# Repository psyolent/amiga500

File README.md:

# RE-Amiga500
Amiga 500+ v8a Re-Imagined.

These files are generated from schematics. Not from a printed circuit board via Sprint (like my A2000 I will soon release)
https://www.amigawiki.org/dnl/schematics/A500_R6.pdf 

I manually routed these traces. The component positioning needs to be checked for accuracy and the mounting holes (at time of release need to be added)

I am releasing these for people to use not for commercial purposes to keep the Amiga alive. It is part of who I am and will live on with me forever along this journey.

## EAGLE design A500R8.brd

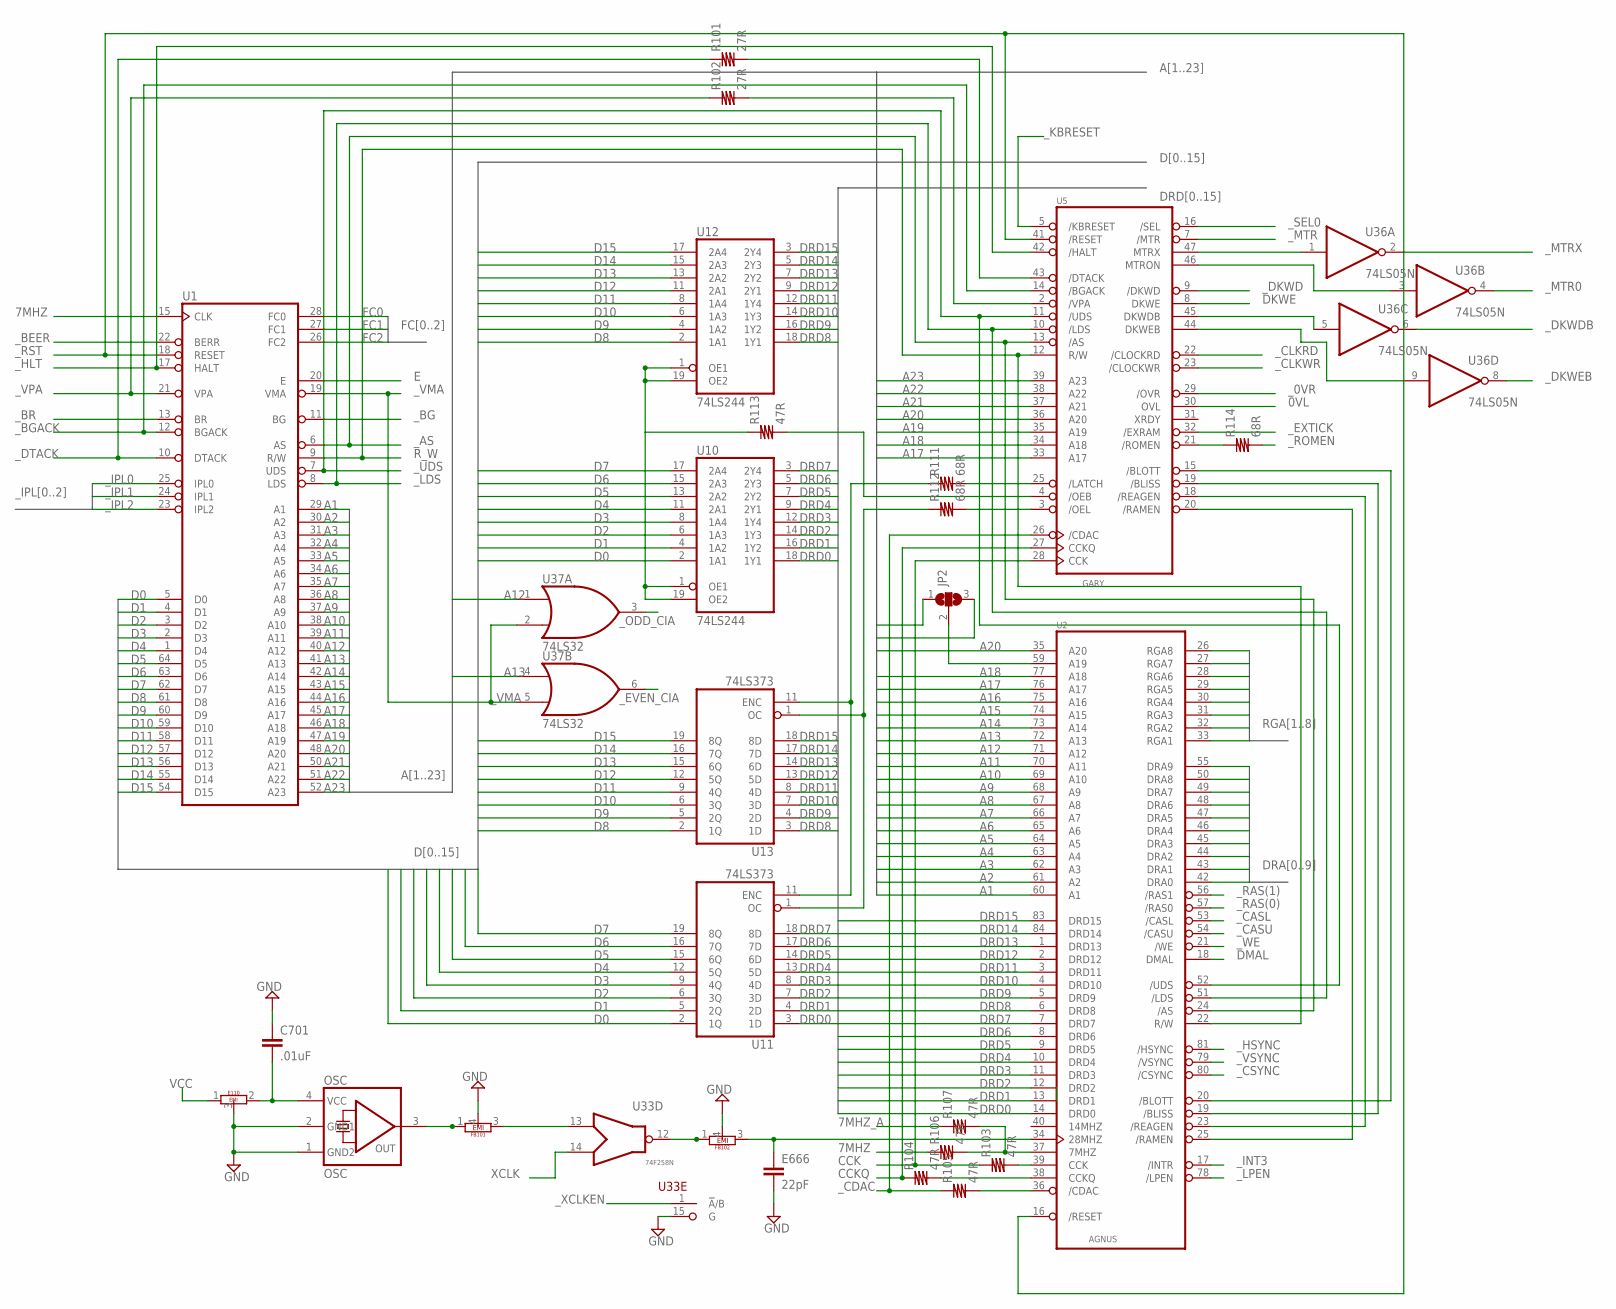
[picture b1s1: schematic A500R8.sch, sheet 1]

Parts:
C701: .01uF; C10B4
E110: EMIFILTER
E666: 22pF; C10B4
FB101: 68R; EMIFILTLONG
FB102: 150; EMIFILTLONG
JP2: SJ2W; SJ_2
OSC: OSC; AMIGACRYSTAL
R101, R102: 27R; R10B4
R103, R104, R105, R106, R107, R113: 47R; R10B4
R111, R112, R114: 68R; R10B4
U1: MC68000P; DIL64
U2: AGNU8375; PLCC84
U5: GARY; DIP48-6
U10, U12: 74LS244; DIL20
U11, U13: 74LS373; DIL20
U33: 74F258N; DIL16
U36: 74LS05N; DIL14
U37: 74LS32; DIL14

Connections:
0VL: U5.30 (OVL); also elsewhere on the board
7MHZ: R106.1, U1.15 (CLK); also elsewhere on the board
7MHZ_A: R107.1; also elsewhere on the board
A1: U1.29 (A1), U2.60 (A1); also elsewhere on the board
A2: U1.30 (A2), U2.61 (A2); also elsewhere on the board
A3: U1.31 (A3), U2.62 (A3); also elsewhere on the board
A4: U1.32 (A4), U2.63 (A4); also elsewhere on the board
A5: U1.33 (A5), U2.64 (A5); also elsewhere on the board
A6: U1.34 (A6), U2.65 (A6); also elsewhere on the board
A7: U1.35 (A7), U2.66 (A7); also elsewhere on the board
A8: U1.36 (A8), U2.67 (A8); also elsewhere on the board
A9: U1.37 (A9), U2.68 (A9); also elsewhere on the board
A10: U1.38 (A10), U2.69 (A10); also elsewhere on the board
A11: U1.39 (A11), U2.70 (A11); also elsewhere on the board
A12: U1.40 (A12), U2.71 (A12), U37.1 (I0); also elsewhere on the board
A13: U1.41 (A13), U2.72 (A13), U37.4 (I0); also elsewhere on the board
A14: U1.42 (A14), U2.73 (A14); also elsewhere on the board
A15: U1.43 (A15), U2.74 (A15); also elsewhere on the board
A16: U1.44 (A16), U2.75 (A16); also elsewhere on the board
A17: U1.45 (A17), U2.76 (A17), U5.33 (A17); also elsewhere on the board
A18: U1.46 (A18), U2.77 (A18), U5.34 (A18); also elsewhere on the board
A19: JP2.3, U1.47 (A19), U5.35 (A19); also elsewhere on the board
A20: U1.48 (A20), U2.35 (A20), U5.36 (A20); also elsewhere on the board
A21: U1.50 (A21), U5.37 (A21); also elsewhere on the board
A22: U1.51 (A22), U5.38 (A22); also elsewhere on the board
A23: JP2.1, U1.52 (A23), U5.39 (A23); also elsewhere on the board
CCK: R103.1, U5.28 (CCK); also elsewhere on the board
CCKQ: R104.1, U5.27 (CCKQ); also elsewhere on the board
D0: U1.5 (D0), U10.2 (1A1), U11.2 (1Q); also elsewhere on the board
D1: U1.4 (D1), U10.4 (1A2), U11.5 (2Q); also elsewhere on the board
D2: U1.3 (D2), U10.6 (1A3), U11.6 (3Q); also elsewhere on the board
D3: U1.2 (D3), U10.8 (1A4), U11.9 (4Q); also elsewhere on the board
D4: U1.1 (D4), U10.11 (2A1), U11.12 (5Q); also elsewhere on the board
D5: U1.64 (D5), U10.13 (2A2), U11.15 (6Q); also elsewhere on the board
D6: U1.63 (D6), U10.15 (2A3), U11.16 (7Q); also elsewhere on the board
D7: U1.62 (D7), U10.17 (2A4), U11.19 (8Q); also elsewhere on the board
D8: U1.61 (D8), U12.2 (1A1), U13.2 (1Q); also elsewhere on the board
D9: U1.60 (D9), U12.4 (1A2), U13.5 (2Q); also elsewhere on the board
D10: U1.59 (D10), U12.6 (1A3), U13.6 (3Q); also elsewhere on the board
D11: U1.58 (D11), U12.8 (1A4), U13.9 (4Q); also elsewhere on the board
D12: U1.57 (D12), U12.11 (2A1), U13.12 (5Q); also elsewhere on the board
D13: U1.56 (D13), U12.13 (2A2), U13.15 (6Q); also elsewhere on the board
D14: U1.55 (D14), U12.15 (2A3), U13.16 (7Q); also elsewhere on the board
D15: U1.54 (D15), U12.17 (2A4), U13.19 (8Q); also elsewhere on the board
DKWE: U5.8 (DKWE); also elsewhere on the board
DMAL: U2.18 (DMAL); also elsewhere on the board
DRA0: U2.42 (DRA0); also elsewhere on the board
DRA1: U2.43 (DRA1); also elsewhere on the board
DRA2: U2.44 (DRA2); also elsewhere on the board
DRA3: U2.45 (DRA3); also elsewhere on the board
DRA4: U2.46 (DRA4); also elsewhere on the board
DRA5: U2.47 (DRA5); also elsewhere on the board
DRA6: U2.48 (DRA6); also elsewhere on the board
DRA7: U2.49 (DRA7); also elsewhere on the board
DRA8: U2.50 (DRA8); also elsewhere on the board
DRA9: U2.55 (DRA9); also elsewhere on the board
DRD0: U2.14 (DRD0), U10.18 (1Y1), U11.3 (1D); also elsewhere on the board
DRD1: U2.13 (DRD1), U10.16 (1Y2), U11.4 (2D); also elsewhere on the board
DRD2: U2.12 (DRD2), U10.14 (1Y3), U11.7 (3D); also elsewhere on the board
DRD3: U2.11 (DRD3), U10.12 (1Y4), U11.8 (4D); also elsewhere on the board
DRD4: U2.10 (DRD4), U10.9 (2Y1), U11.13 (5D); also elsewhere on the board
DRD5: U2.9 (DRD5), U10.7 (2Y2), U11.14 (6D); also elsewhere on the board
DRD6: U2.8 (DRD6), U10.5 (2Y3), U11.17 (7D); also elsewhere on the board
DRD7: U2.7 (DRD7), U10.3 (2Y4), U11.18 (8D); also elsewhere on the board
DRD8: U2.6 (DRD8), U12.18 (1Y1), U13.3 (1D); also elsewhere on the board
DRD9: U2.5 (DRD9), U12.16 (1Y2), U13.4 (2D); also elsewhere on the board
DRD10: U2.4 (DRD10), U12.14 (1Y3), U13.7 (3D); also elsewhere on the board
DRD11: U2.3 (DRD11), U12.12 (1Y4), U13.8 (4D); also elsewhere on the board
DRD12: U2.2 (DRD12), U12.9 (2Y1), U13.13 (5D); also elsewhere on the board
DRD13: U2.1 (DRD13), U12.7 (2Y2), U13.14 (6D); also elsewhere on the board
DRD14: U2.84 (DRD14), U12.5 (2Y3), U13.17 (7D); also elsewhere on the board
DRD15: U2.83 (DRD15), U12.3 (2Y4), U13.18 (8D); also elsewhere on the board
E: U1.20 (E); also elsewhere on the board
FC0: U1.28 (FC0); also elsewhere on the board
FC1: U1.27 (FC1); also elsewhere on the board
FC2: U1.26 (FC2); also elsewhere on the board
GND: C701.1, E110.3, E666.2, FB101.4, FB102.4, OSC.1 (GND2), OSC.2 (GND1), U2.41 (GND), U2.58 (GND), U2.82 (GND), U5.1 (GND), U5.24 (GND), U5.40 (GND), U33.15 (G); also elsewhere on the board
unnamed: R113.1, U10.1 (OE1), U10.19 (OE2), U12.1 (OE1), U12.19 (OE2)
unnamed: R113.2, U5.4 (/OEB)
unnamed: R112.1, U11.1 (OC), U13.1 (OC)
unnamed: R112.2, U5.3 (/OEL)
unnamed: R111.1, U11.11 (ENC), U13.11 (ENC)
unnamed: R111.2, U5.25 (/LATCH)
unnamed: R102.2, U5.2 (/VPA)
unnamed: R114.1, U5.21 (/ROMEN)
unnamed: U5.47 (MTRX), U36.1 (I)
unnamed: R101.2, U5.43 (/DTACK)
unnamed: R106.2, R107.2, U2.37 (7MHZ)
unnamed: R103.2, U2.39 (CCK)
unnamed: R104.2, U2.38 (CCKQ)
unnamed: R105.2, U2.36 (/CDAC)
unnamed: U2.20 (/BLOTT), U5.15 (/BLOTT)
unnamed: U2.19 (/BLISS), U5.19 (/BLISS)
unnamed: U2.23 (/REAGEN), U5.18 (/REAGEN)
unnamed: U2.25 (/RAMEN), U5.20 (/RAMEN)
unnamed: E666.1, FB102.3, U2.34 (28MHZ)
unnamed: JP2.2, U2.59 (A19)
unnamed: U5.46 (MTRON), U36.3 (I)
unnamed: U5.45 (DKWDB), U36.5 (I)
unnamed: U5.44 (DKWEB), U36.9 (I)
unnamed: FB102.1, FB102.2, U33.12 (O)
unnamed: FB101.1, FB101.2, OSC.3 (OUT)
unnamed: FB101.3, U33.13 (I0)
unnamed: C701.2, E110.2, OSC.4 (VCC)
RGA1: U2.33 (RGA1); also elsewhere on the board
RGA2: U2.32 (RGA2); also elsewhere on the board
RGA3: U2.31 (RGA3); also elsewhere on the board
RGA4: U2.30 (RGA4); also elsewhere on the board
RGA5: U2.29 (RGA5); also elsewhere on the board
RGA6: U2.28 (RGA6); also elsewhere on the board
RGA7: U2.27 (RGA7); also elsewhere on the board
RGA8: U2.26 (RGA8); also elsewhere on the board
R_W: U1.9 (R/W), U2.22 (R/W), U5.12 (R/W); also elsewhere on the board
VCC: E110.1; also elsewhere on the board
XCLK: U33.14 (I1); also elsewhere on the board
_0VR: U5.29 (/OVR); also elsewhere on the board
_AS: U1.6 (AS), U2.24 (/AS), U5.13 (/AS); also elsewhere on the board
_BEER: U1.22 (BERR); also elsewhere on the board
_BG: U1.11 (BG); also elsewhere on the board
_BGACK: U1.12 (BGACK), U5.14 (/BGACK); also elsewhere on the board
_BR: U1.13 (BR); also elsewhere on the board
_CASL: U2.53 (/CASL); also elsewhere on the board
_CASU: U2.54 (/CASU); also elsewhere on the board
_CDAC: R105.1, U5.26 (/CDAC); also elsewhere on the board
_CLKRD: U5.22 (/CLOCKRD); also elsewhere on the board
_CLKWR: U5.23 (/CLOCKWR); also elsewhere on the board
_CSYNC: U2.80 (/CSYNC); also elsewhere on the board
_DKWD: U5.9 (/DKWD); also elsewhere on the board
_DKWDB: U36.6 (O); also elsewhere on the board
_DKWEB: U36.8 (O); also elsewhere on the board
_DTACK: R101.1, U1.10 (DTACK); also elsewhere on the board
_EVEN_CIA: U37.6 (O); also elsewhere on the board
_EXTICK: U5.32 (/EXRAM); also elsewhere on the board
_HLT: U1.17 (HALT), U5.42 (/HALT); also elsewhere on the board
_HSYNC: U2.81 (/HSYNC); also elsewhere on the board
_INT3: U2.17 (/INTR); also elsewhere on the board
_IPL0: U1.25 (IPL0); also elsewhere on the board
_IPL1: U1.24 (IPL1); also elsewhere on the board
_IPL2: U1.23 (IPL2); also elsewhere on the board
_KBRESET: U5.5 (/KBRESET); also elsewhere on the board
_LDS: U1.8 (LDS), U2.51 (/LDS), U5.10 (/LDS); also elsewhere on the board
_LPEN: U2.78 (/LPEN); also elsewhere on the board
_MTR: U5.7 (/MTR); also elsewhere on the board
_MTR0: U36.4 (O); also elsewhere on the board
_MTRX: U36.2 (O); also elsewhere on the board
_ODD_CIA: U37.3 (O); also elsewhere on the board
_RAS(0): U2.57 (/RAS0); also elsewhere on the board
_RAS(1): U2.56 (/RAS1); also elsewhere on the board
_ROMEN: R114.2; also elsewhere on the board
_RST: U1.18 (RESET), U2.16 (/RESET), U5.41 (/RESET); also elsewhere on the board
_SEL0: U5.16 (/SEL); also elsewhere on the board
_UDS: U1.7 (UDS), U2.52 (/UDS), U5.11 (/UDS); also elsewhere on the board
_VMA: U1.19 (VMA), U37.2 (I1), U37.5 (I1); also elsewhere on the board
_VPA: R102.1, U1.21 (VPA); also elsewhere on the board
_VSYNC: U2.79 (/VSYNC); also elsewhere on the board
_WE: U2.21 (/WE); also elsewhere on the board
_XCLKEN: U33.1 (!A!/B); also elsewhere on the board

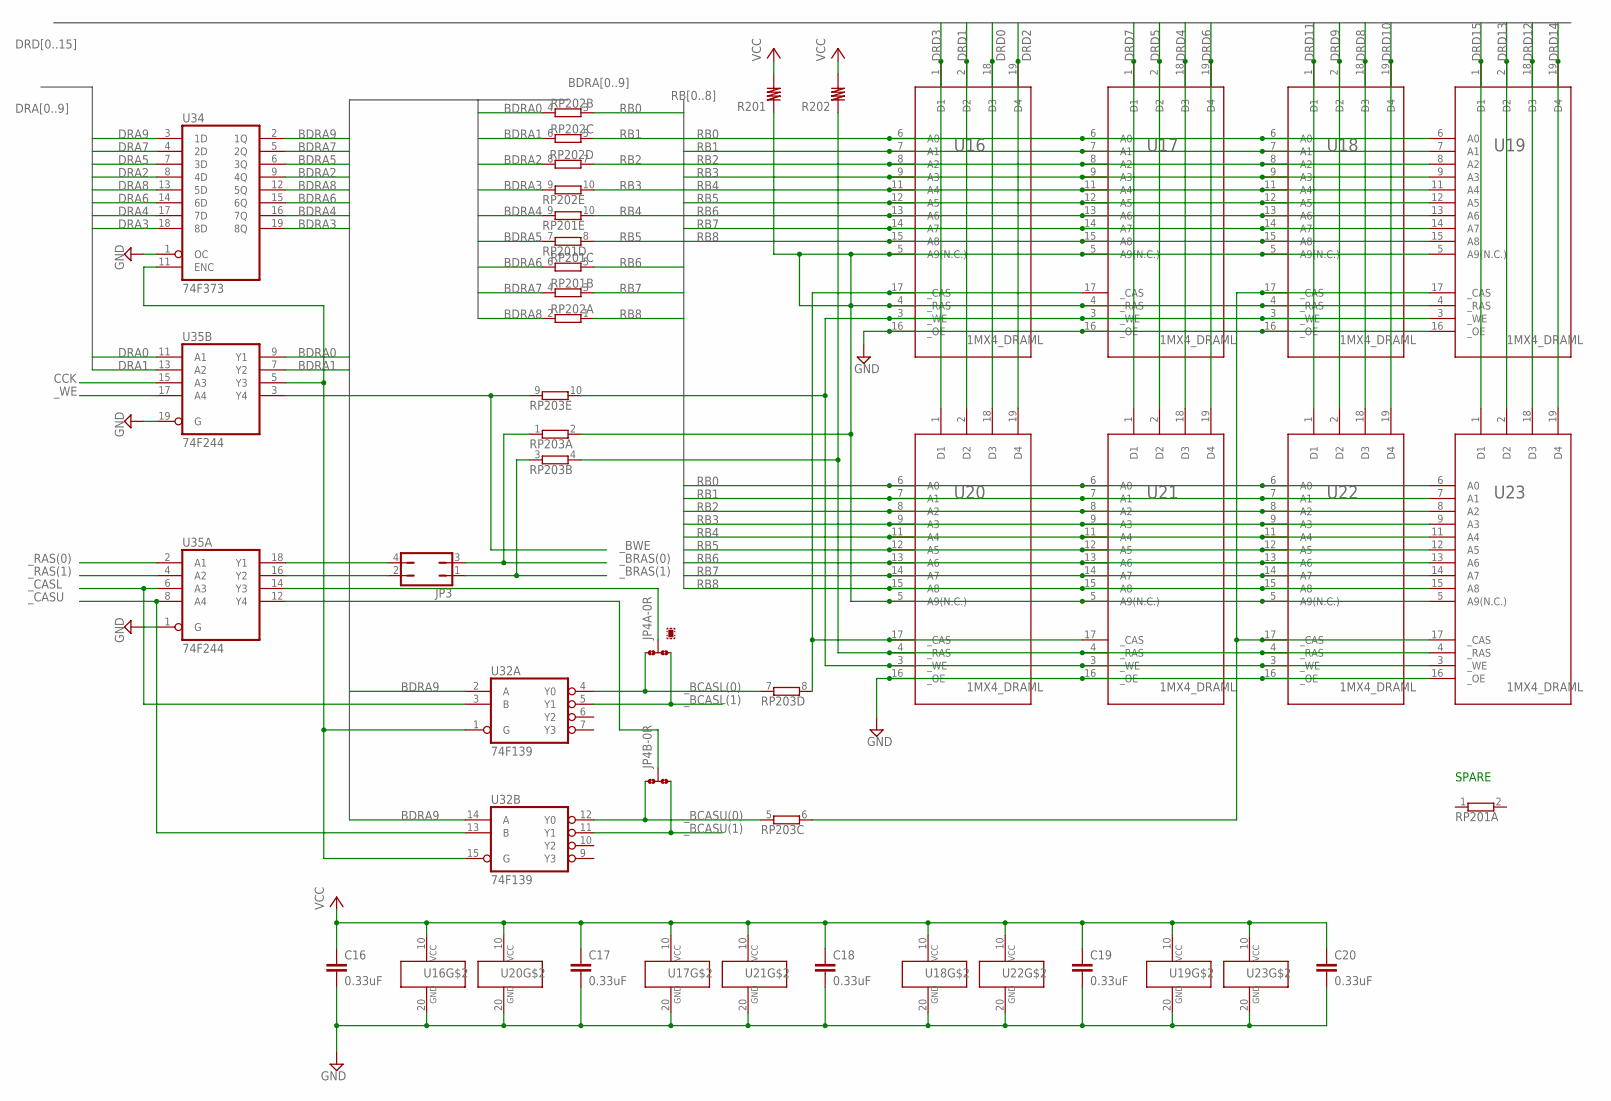
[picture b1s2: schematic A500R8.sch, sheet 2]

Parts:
C16, C17, C18, C19, C20: 0.33uF; C10B4
JP3: JP2Q
JP4A: JP4A; A0R-JMP
JP4B: JP4B; A0R-JMP
R201, R202: R10/4; R10B4
RP201, RP202, RP203: E5R; SIL10
U16, U17, U18, U19, U20, U21, U22, U23: 1MX4_DRAML; DIL20
U32: 74F139; DIL16
U34: 74F373; DIL20
U35: 74F244; DIL20

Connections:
BDRA0: RP202.4 (2), U35.9 (Y1); also elsewhere on the board
BDRA1: RP202.6 (2), U35.7 (Y2); also elsewhere on the board
BDRA2: RP202.8 (2), U34.9 (4Q); also elsewhere on the board
BDRA3: RP202.9 (1), U34.19 (8Q); also elsewhere on the board
BDRA4: RP201.9 (1), U34.16 (7Q); also elsewhere on the board
BDRA5: RP201.7 (1), U34.6 (3Q); also elsewhere on the board
BDRA6: RP201.6 (2), U34.15 (6Q); also elsewhere on the board
BDRA7: RP201.4 (2), U34.5 (2Q); also elsewhere on the board
BDRA8: RP202.2, U34.12 (5Q); also elsewhere on the board
BDRA9: U32.2 (A), U32.14 (A), U34.2 (1Q)
CCK: U35.15 (A3); also elsewhere on the board
DRA0: U35.11 (A1); also elsewhere on the board
DRA1: U35.13 (A2); also elsewhere on the board
DRA2: U34.8 (4D); also elsewhere on the board
DRA3: U34.18 (8D); also elsewhere on the board
DRA4: U34.17 (7D); also elsewhere on the board
DRA5: U34.7 (3D); also elsewhere on the board
DRA6: U34.14 (6D); also elsewhere on the board
DRA7: U34.4 (2D); also elsewhere on the board
DRA8: U34.13 (5D); also elsewhere on the board
DRA9: U34.3 (1D); also elsewhere on the board
DRD0: U16.18 (D3), U20.18 (D3); also elsewhere on the board
DRD1: U16.2 (D2), U20.2 (D2); also elsewhere on the board
DRD2: U16.19 (D4), U20.19 (D4); also elsewhere on the board
DRD3: U16.1 (D1), U20.1 (D1); also elsewhere on the board
DRD4: U17.18 (D3), U21.18 (D3); also elsewhere on the board
DRD5: U17.2 (D2), U21.2 (D2); also elsewhere on the board
DRD6: U17.19 (D4), U21.19 (D4); also elsewhere on the board
DRD7: U17.1 (D1), U21.1 (D1); also elsewhere on the board
DRD8: U18.18 (D3), U22.18 (D3); also elsewhere on the board
DRD9: U18.2 (D2), U22.2 (D2); also elsewhere on the board
DRD10: U18.19 (D4), U22.19 (D4); also elsewhere on the board
DRD11: U18.1 (D1), U22.1 (D1); also elsewhere on the board
DRD12: U19.18 (D3), U23.18 (D3); also elsewhere on the board
DRD13: U19.2 (D2), U23.2 (D2); also elsewhere on the board
DRD14: U19.19 (D4), U23.19 (D4); also elsewhere on the board
DRD15: U19.1 (D1), U23.1 (D1); also elsewhere on the board
GND: C16.2, C17.2, C18.2, C19.2, C20.2, U16.16 (_OE), U16.20 (GND1), U17.16 (_OE), U17.20 (GND1), U18.16 (_OE), U18.20 (GND1), U19.16 (_OE), U19.20 (GND1), U20.16 (_OE), U20.20 (GND1), U21.16 (_OE), U21.20 (GND1), U22.16 (_OE), U22.20 (GND1), U23.16 (_OE), U23.20 (GND1), U34.1 (OC), U35.1 (G), U35.19 (G); also elsewhere on the board
unnamed: U32.1 (G), U32.15 (G), U34.11 (ENC), U35.5 (Y3)
unnamed: JP3.4, U35.18 (Y1)
unnamed: JP3.2, U35.16 (Y2)
unnamed: JP4A.2, U35.14 (Y3)
unnamed: JP4B.2, U35.12 (Y4)
unnamed: R202.1, RP203.4 (2), U20.4 (_RAS), U21.4 (_RAS), U22.4 (_RAS), U23.4 (_RAS)
unnamed: RP203.6 (2), U18.17 (_CAS), U19.17 (_CAS), U22.17 (_CAS), U23.17 (_CAS)
unnamed: RP203.8 (2), U16.17 (_CAS), U17.17 (_CAS), U20.17 (_CAS), U21.17 (_CAS)
unnamed: RP203.10 (2), U16.3 (_WE), U17.3 (_WE), U18.3 (_WE), U19.3 (_WE), U20.3 (_WE), U21.3 (_WE), U22.3 (_WE), U23.3 (_WE)
unnamed: R201.1, RP203.2, U16.4 (_RAS), U16.5 (A9(N.C.)), U17.4 (_RAS), U17.5 (A9(N.C.)), U18.4 (_RAS), U18.5 (A9(N.C.)), U19.4 (_RAS), U19.5 (A9(N.C.)), U20.5 (A9(N.C.)), U21.5 (A9(N.C.)), U22.5 (A9(N.C.)), U23.5 (A9(N.C.))
RB0: RP202.3 (1), U16.6 (A0), U17.6 (A0), U18.6 (A0), U19.6 (A0), U20.6 (A0), U21.6 (A0), U22.6 (A0), U23.6 (A0)
RB1: RP202.5 (1), U16.7 (A1), U17.7 (A1), U18.7 (A1), U19.7 (A1), U20.7 (A1), U21.7 (A1), U22.7 (A1), U23.7 (A1)
RB2: RP202.7 (1), U16.8 (A2), U17.8 (A2), U18.8 (A2), U19.8 (A2), U20.8 (A2), U21.8 (A2), U22.8 (A2), U23.8 (A2)
RB3: RP202.10 (2), U16.9 (A3), U17.9 (A3), U18.9 (A3), U19.9 (A3), U20.9 (A3), U21.9 (A3), U22.9 (A3), U23.9 (A3)
RB4: RP201.10 (2), U16.11 (A4), U17.11 (A4), U18.11 (A4), U19.11 (A4), U20.11 (A4), U21.11 (A4), U22.11 (A4), U23.11 (A4)
RB5: RP201.8 (2), U16.12 (A5), U17.12 (A5), U18.12 (A5), U19.12 (A5), U20.12 (A5), U21.12 (A5), U22.12 (A5), U23.12 (A5)
RB6: RP201.5 (1), U16.13 (A6), U17.13 (A6), U18.13 (A6), U19.13 (A6), U20.13 (A6), U21.13 (A6), U22.13 (A6), U23.13 (A6)
RB7: RP201.3 (1), U16.14 (A7), U17.14 (A7), U18.14 (A7), U19.14 (A7), U20.14 (A7), U21.14 (A7), U22.14 (A7), U23.14 (A7)
RB8: RP202.1, U16.15 (A8), U17.15 (A8), U18.15 (A8), U19.15 (A8), U20.15 (A8), U21.15 (A8), U22.15 (A8), U23.15 (A8)
VCC: C16.1, C17.1, C18.1, C19.1, C20.1, R201.2, R202.2, U16.10 (VCC1), U17.10 (VCC1), U18.10 (VCC1), U19.10 (VCC1), U20.10 (VCC1), U21.10 (VCC1), U22.10 (VCC1), U23.10 (VCC1); also elsewhere on the board
_BCASL(0): JP4A.1, RP203.7 (1), U32.4 (Y0)
_BCASL(1): JP4A.3, U32.5 (Y1); also elsewhere on the board
_BCASU(0): JP4B.1, RP203.5 (1), U32.12 (Y0)
_BCASU(1): JP4B.3, U32.11 (Y1); also elsewhere on the board
_BRAS(0): JP3.3, RP203.1; also elsewhere on the board
_BRAS(1): JP3.1, RP203.3 (1); also elsewhere on the board
_BWE: RP203.9 (1), U35.3 (Y4); also elsewhere on the board
_CASL: U32.3 (B), U35.6 (A3); also elsewhere on the board
_CASU: U32.13 (B), U35.8 (A4); also elsewhere on the board
_RAS(0): U35.2 (A1); also elsewhere on the board
_RAS(1): U35.4 (A2); also elsewhere on the board
_WE: U35.17 (A4); also elsewhere on the board

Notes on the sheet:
SPARE

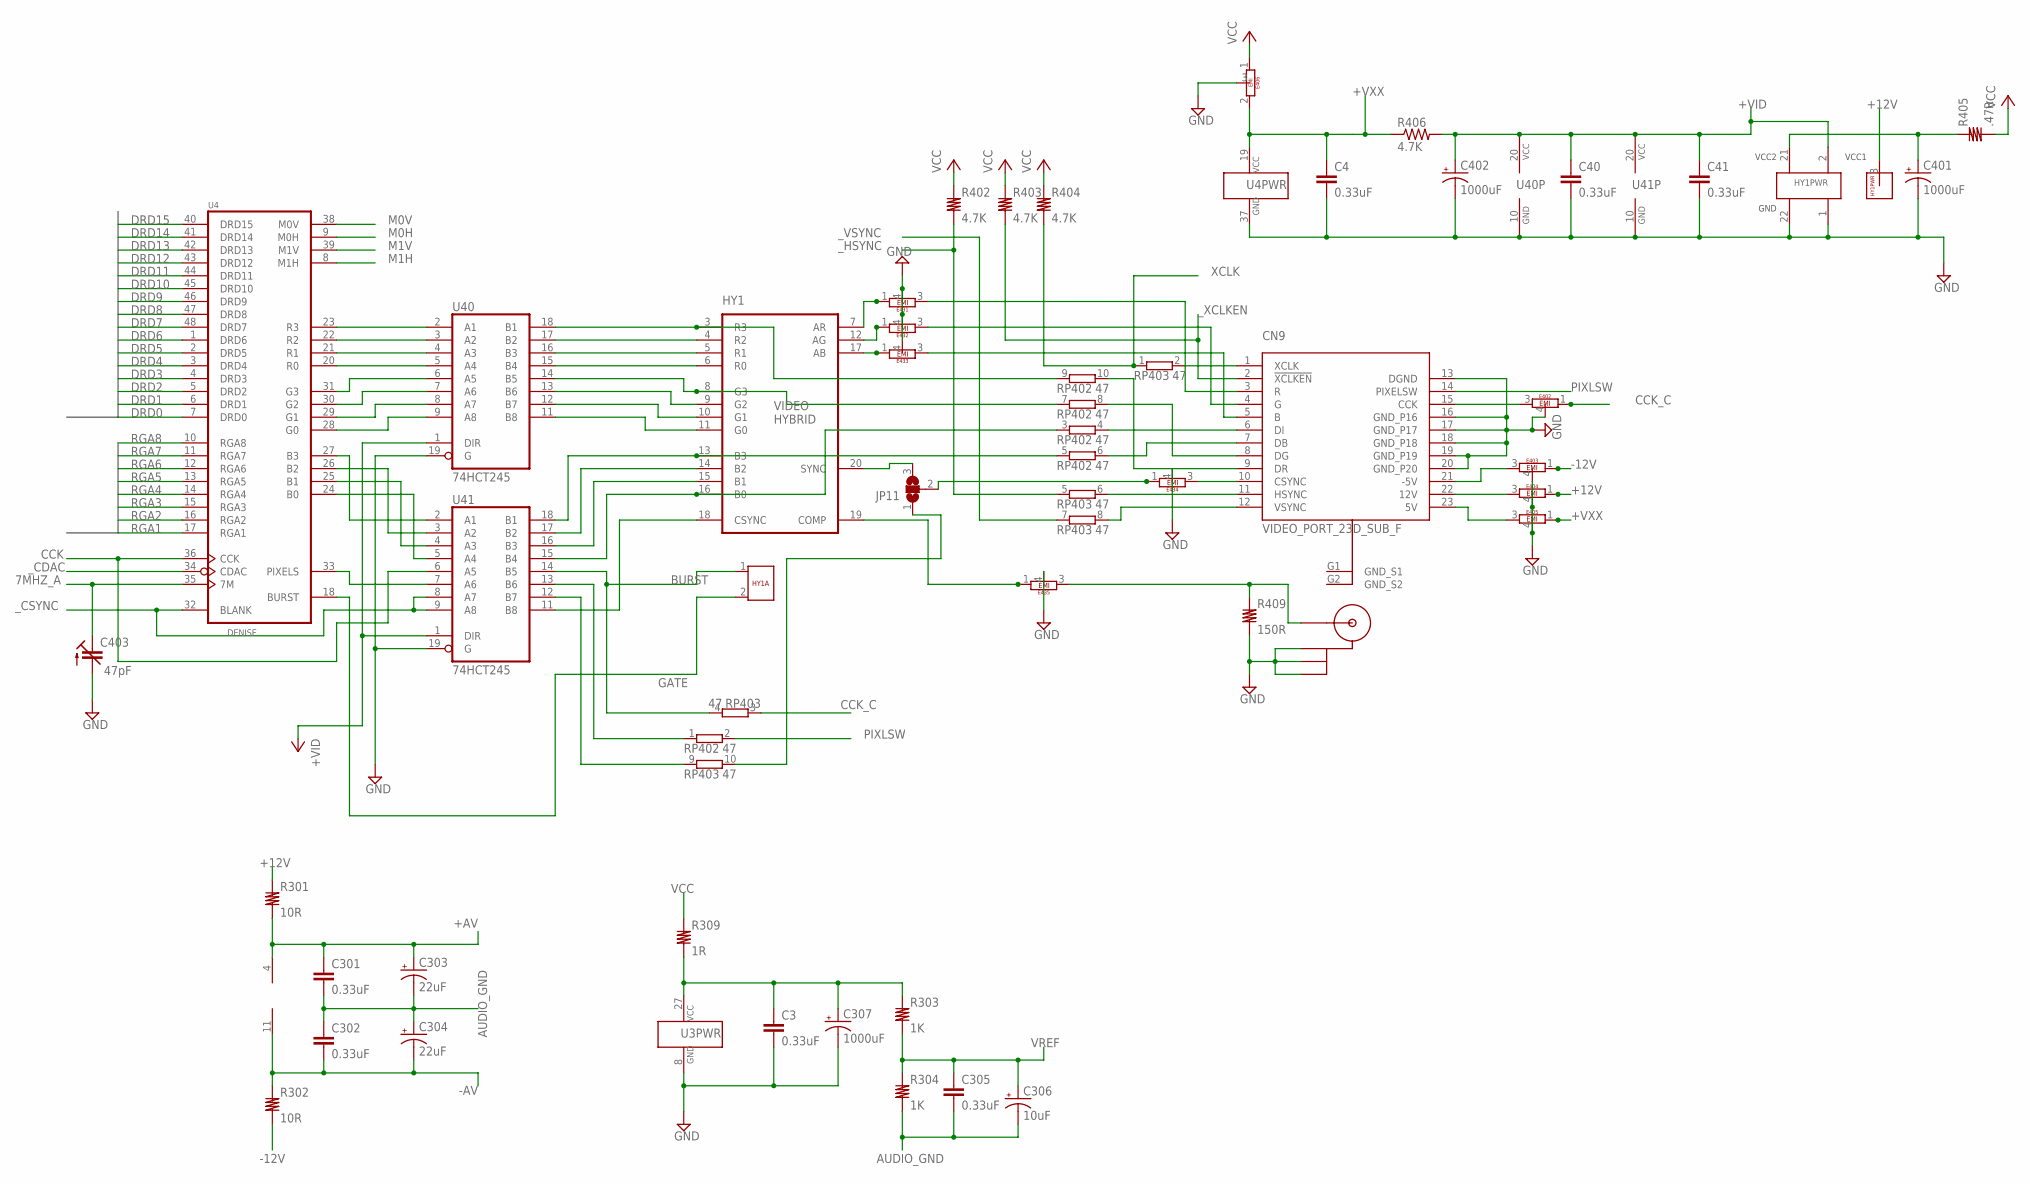
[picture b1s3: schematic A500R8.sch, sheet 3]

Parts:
C3, C4, C40, C41, C301, C302, C305: 0.33uF; C10B4
C303, C304: 22uF; E5-6
C306: 10uF; E5-6
C307: 1000uF; E5-6
C401, C402: 1000uF; E5-10,5
C403: 47pF; CTRIM3050.504
CN9: VIDEO_PORT_23D_SUB_F; F23H_FC
CN10: CINCH; CINCH-B
E402: 150pF; EMIFILTLONG
E403, E404, E405, E431, E432, E433, E434, E435: EMIFILTERLONG; EMIFILTLONG
E406: EMIFILTER
HY1: HY1; SIP22
JP11: SJ2W; SJ_2
R301, R302: 10R; R10B4
R303, R304: 1K; R10B4
R309: 1R; R10B4
R402, R403, R404: 4.7K; R10B4
R405: .47R; R10B4
R406: 4.7K; 0207/10
R409: 150R; R10B4
RP402, RP403: 47; SIL10
U3: PAULA_DIP; DIP48-6
U4: DENISE HR; DIP48-6
U14: LF347/TL084; DIL14
U40, U41: 74HCT245; DIL20
U$1: HY1A

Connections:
7MHZ_A: C403.1 (E), U4.35 (7M); also elsewhere on the board
+12V: E404.1, E404.2, R301.1, U$1.3; also elsewhere on the board
+AV: C301.1, C303.+, R301.2, U14.4 (V+); also elsewhere on the board
+VID: C40.1, C41.1, C402.+, HY1.2 (VCC), R406.2, U40.1 (DIR), U40.20 (VCC), U41.1 (DIR), U41.20 (VCC)
+VXX: C4.1, E405.1, E405.2, E406.2, R406.1, U4.19 (VCC1)
-12V: E403.1, E403.2, R302.2; also elsewhere on the board
-AV: C302.2, C304.-, R302.1, U14.11 (V-); also elsewhere on the board
AUDIO_GND: C301.2, C302.1, C303.-, C304.+, C305.2, C306.-, R304.2; also elsewhere on the board
BURST: RP403.4 (2), U41.14 (B5), U$1.1
CCK: U4.36 (CCK), U41.6 (A5); also elsewhere on the board
CCK_C: E402.1, E402.2, RP403.3 (1)
DRD0: U4.7 (DRD0); also elsewhere on the board
DRD1: U4.6 (DRD1); also elsewhere on the board
DRD2: U4.5 (DRD2); also elsewhere on the board
DRD3: U4.4 (DRD3); also elsewhere on the board
DRD4: U4.3 (DRD4); also elsewhere on the board
DRD5: U4.2 (DRD5); also elsewhere on the board
DRD6: U4.1 (DRD6); also elsewhere on the board
DRD7: U4.48 (DRD7); also elsewhere on the board
DRD8: U4.47 (DRD8); also elsewhere on the board
DRD9: U4.46 (DRD9); also elsewhere on the board
DRD10: U4.45 (DRD10); also elsewhere on the board
DRD11: U4.44 (DRD11); also elsewhere on the board
DRD12: U4.43 (DRD12); also elsewhere on the board
DRD13: U4.42 (DRD13); also elsewhere on the board
DRD14: U4.41 (DRD14); also elsewhere on the board
DRD15: U4.40 (DRD15); also elsewhere on the board
GATE: U4.18 (BURST), U$1.2
GND: C3.2, C4.2, C40.2, C41.2, C307.-, C401.-, C402.-, C403.2 (A), CN9.13 (DGND), CN9.16 (GND_P16), CN9.17 (GND_P17), CN9.18 (GND_P18), CN9.19 (GND_P19), CN9.20 (GND_P20), CN10.P$2, CN10.P$3, CN10.P$4, E402.4, E403.4, E404.4, E405.4, E406.3, E431.4, E432.4, E433.4, E434.4, E435.4, HY1.1 (GND), HY1.22 (GND), R409.2, U3.8 (GND1), U4.37 (GND1), U40.10 (GND), U40.19 (G), U41.10 (GND), U41.19 (G); also elsewhere on the board
GND_S1: CN9.G1 (GND_S1); also elsewhere on the board
GND_S2: CN9.G2 (GND_S2); also elsewhere on the board
M0H: U4.9 (M0H); also elsewhere on the board
M0V: U4.38 (M0V); also elsewhere on the board
M1H: U4.8 (M1H); also elsewhere on the board
M1V: U4.39 (M1V); also elsewhere on the board
unnamed: U4.23 (R3), U40.2 (A1)
unnamed: U4.22 (R2), U40.3 (A2)
unnamed: U4.21 (R1), U40.4 (A3)
unnamed: U4.20 (R0), U40.5 (A4)
unnamed: U4.31 (G3), U40.6 (A5)
unnamed: U4.30 (G2), U40.7 (A6)
unnamed: U4.29 (G1), U40.8 (A7)
unnamed: U4.28 (G0), U40.9 (A8)
unnamed: JP11.1, RP403.10 (2)
unnamed: U4.26 (B2), U41.3 (A2)
unnamed: U4.27 (B3), U41.2 (A1)
unnamed: U4.25 (B1), U41.4 (A3)
unnamed: U4.24 (B0), U41.5 (A4)
unnamed: U4.33 (PIXELS), U41.7 (A6)
unnamed: C3.1, C307.+, R303.1, R309.2, U3.27 (VCC1)
unnamed: E434.1, E434.2, JP11.2
unnamed: HY1.4 (R2), U40.17 (B2)
unnamed: HY1.5 (R1), U40.16 (B3)
unnamed: HY1.6 (R0), U40.15 (B4)
unnamed: HY1.8 (G3), RP402.7 (1), U40.14 (B5)
unnamed: HY1.9 (G2), U40.13 (B6)
unnamed: HY1.10 (G1), U40.12 (B7)
unnamed: HY1.11 (G0), U40.11 (B8)
unnamed: HY1.13 (B3), RP402.5 (1), U41.18 (B1)
unnamed: HY1.14 (B2), U41.17 (B2)
unnamed: HY1.15 (B1), U41.16 (B3)
unnamed: HY1.18 (CSYNC), U41.11 (B8)
unnamed: HY1.20 (SYNC), JP11.3
unnamed: RP402.1, U41.13 (B6)
unnamed: RP403.9 (1), U41.12 (B7)
unnamed: E435.1, E435.2, HY1.19 (COMP)
unnamed: CN9.1 (XCLK), RP403.2
unnamed: CN9.6 (DI), RP402.4 (2)
unnamed: HY1.16 (B0), RP402.3 (1), U41.15 (B4)
unnamed: CN9.7 (DB), RP402.6 (2)
unnamed: CN9.8 (DG), RP402.8 (2)
unnamed: CN9.9 (DR), RP402.10 (2)
unnamed: CN9.10 (CSYNC), E434.3
unnamed: CN9.11 (HSYNC), RP403.6 (2)
unnamed: CN9.12 (VSYNC), RP403.8 (2)
unnamed: E431.1, E431.2, HY1.7 (AR)
unnamed: E432.1, E432.2, HY1.12 (AG)
unnamed: E433.1, E433.2, HY1.17 (AB)
unnamed: CN9.3 (R), E431.3
unnamed: CN9.5 (B), E433.3
unnamed: CN9.4 (G), E432.3
unnamed: CN10.S, E435.3, R409.1
unnamed: CN9.15 (CCK), E402.3
unnamed: CN9.23 (5V), E405.3
unnamed: CN9.22 (12V), E404.3
unnamed: CN9.21 (-5V), E403.3
unnamed: C401.+, HY1.21 (VCC), R405.1
unnamed: HY1.3 (R3), RP402.9 (1), U40.18 (B1)
PIXLSW: CN9.14 (PIXELSW), RP402.2
RGA1: U4.17 (RGA1); also elsewhere on the board
RGA2: U4.16 (RGA2); also elsewhere on the board
RGA3: U4.15 (RGA3); also elsewhere on the board
RGA4: U4.14 (RGA4); also elsewhere on the board
RGA5: U4.13 (RGA5); also elsewhere on the board
RGA6: U4.12 (RGA6); also elsewhere on the board
RGA7: U4.11 (RGA7); also elsewhere on the board
RGA8: U4.10 (RGA8); also elsewhere on the board
VCC: E406.1, R309.1, R402.1, R403.1, R404.1, R405.2; also elsewhere on the board
VREF: C305.1, C306.+, R303.2, R304.1; also elsewhere on the board
XCLK: R404.2, RP403.1; also elsewhere on the board
_CDAC: U4.34 (CDAC); also elsewhere on the board
_CSYNC: U4.32 (BLANK), U41.8 (A7), U41.9 (A8); also elsewhere on the board
_HSYNC: R402.2, RP403.5 (1); also elsewhere on the board
_VSYNC: RP403.7 (1); also elsewhere on the board
_XCLKEN: CN9.2 (!XCLKEN!), R403.2; also elsewhere on the board
